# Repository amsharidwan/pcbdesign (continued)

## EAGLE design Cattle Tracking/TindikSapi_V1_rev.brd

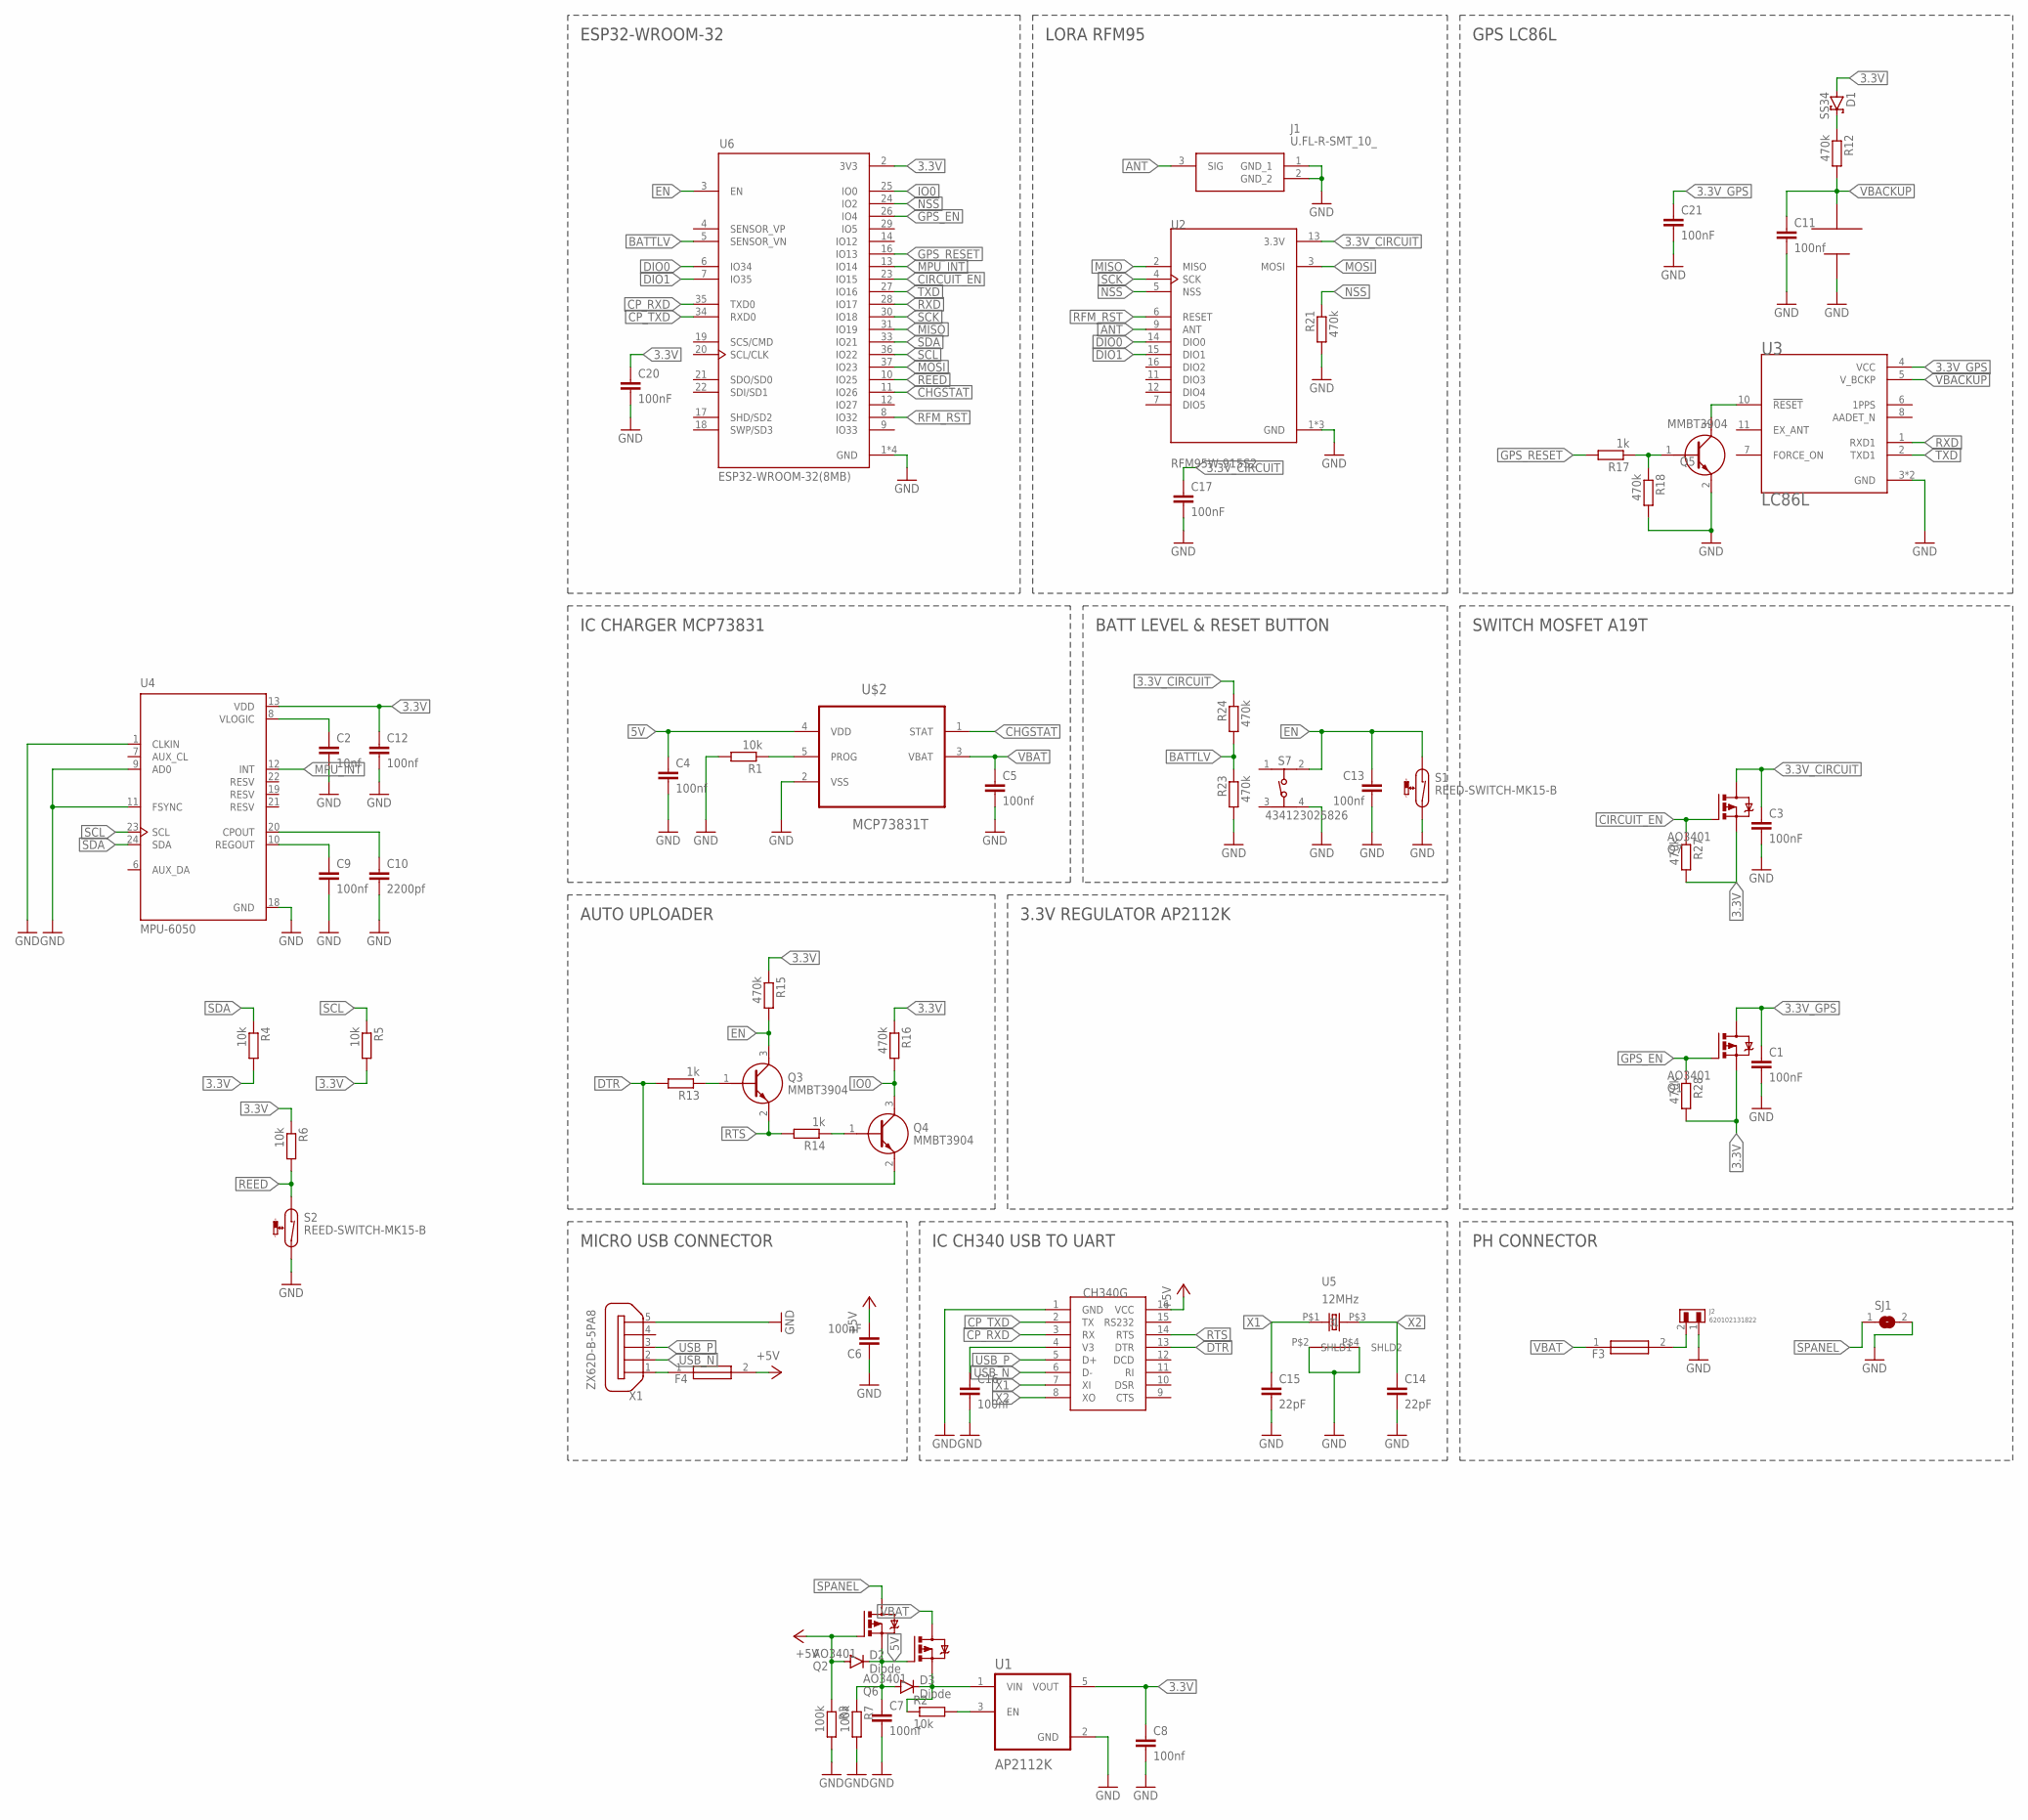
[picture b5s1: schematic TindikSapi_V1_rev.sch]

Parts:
C1, C3, C6, C17, C20, C21: 100nF; C0603
C2: 10nf; C0603
C4, C5, C7, C8, C9, C11, C12, C13, C16: 100nf; C0603
C10: 2200pf; C0603
C14, C15: 22pF; C0603
D1: SS34; SMA
D2, D3: Diode; SOD123
F3, F4: FUSE 1A; FUSC3216X100N
J1: U.FL-R-SMT_10_; UFLRSMT10
J2: 620102131822
Q1, Q2, Q6, Q7: AO3401; SOT23
Q3, Q4, Q5: MMBT3904; SOT95P240X120-3N
R1, R2, R4, R5, R6: 10k; R0603
R3, R7: 100k; R0603
R12, R15, R16, R18, R21, R23, R24, R27, R28: 470k; R0603
R13, R14, R17: 1k; R0603
S1, S2: REED-SWITCH-MK15-B; MK15
S7: 434123025826
SJ1: SJW
U1: AP2112K; SOT95P285X140-5N
U2: RFM95W-915S2; XCVR_RFM95W-915S2
U3: LC86L; XCVR_L86-M33
U4: MPU-6050; QFN50P400X400X95-24N
U5: 12MHz; NX32256A
U6: ESP32-WROOM-32(8MB); MODULE_ESP32-WROOM-32(8MB)
U$2: MCP73831T; SOT95P280X145-5N
U$3: MS621FE
U$5: CH340G; SOIC127P600X175-16N
X1: ZX62D-B-5PA8

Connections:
3.3V: C8.1, C12.1, C20.1, D1.A, Q1.2 (S), Q7.2 (S), R4.2, R5.2, R6.1, R15.1, R16.1, R27.2, R28.2, U1.5 (VOUT), U4.13 (VDD), U6.2 (3V3)
3.3V_CIRCUIT: C3.1, C17.1, Q7.3 (D), R24.1, U2.13 (3.3V)
3.3V_GPS: C1.1, C21.1, Q1.3 (D), U3.4 (VCC)
5V: C4.1, C7.1, D2.C, D3.A, Q2.2 (S), Q6.1 (G), R7.1, U$2.4 (VDD)
+5V: C6.2, D2.A, F4.2, Q2.1 (G), R3.1, U$5.16 (VCC)
ANT: J1.3 (SIG), U2.9 (ANT)
BATTLV: R23.1, R24.2, U6.5 (SENSOR_VN)
CHGSTAT: U6.11 (IO26), U$2.1 (STAT)
CIRCUIT_EN: Q7.1 (G), R27.1, U6.23 (IO15)
CP_RXD: U6.35 (TXD0), U$5.3 (RX)
CP_TXD: U6.34 (RXD0), U$5.2 (TX)
DIO0: U2.14 (DIO0), U6.6 (IO34)
DIO1: U2.15 (DIO1), U6.7 (IO35)
DTR: Q4.2 (E), R13.2, U$5.13 (DTR)
EN: C13.1, Q3.3 (C), R15.2, S1.1, S7.2, U6.3 (EN)
GND: C1.2, C2.2, C3.2, C4.2, C5.2, C6.1, C7.2, C8.2, C9.2, C10.2, C11.2, C12.2, C13.2, C14.2, C15.2, C16.2, C17.2, C20.2, C21.2, J1.1 (GND_1), J1.2 (GND_2), J2.1, Q5.2 (E), R1.2, R3.2, R7.2, R18.2, R21.2, R23.2, S1.2, S2.2, S7.4, SJ1.2, U1.2 (GND), U2.1 (GND), U2.8 (GND), U2.10 (GND), U3.3 (GND), U3.12 (GND), U4.1 (CLKIN), U4.9 (AD0), U4.11 (FSYNC), U4.18 (GND), U5.P$2 (SHLD1), U5.P$4 (SHLD2), U6.1 (GND), U6.15 (GND), U6.38 (GND), U6.39 (GND), U$2.2 (VSS), U$3.V-, U$5.1 (GND), X1.5
GPS_EN: Q1.1 (G), R28.1, U6.26 (IO4)
GPS_RESET: R17.2, U6.16 (IO13)
IO0: Q4.3 (C), R16.2, U6.25 (IO0)
MISO: U2.2 (MISO), U6.31 (IO19)
MOSI: U2.3 (MOSI), U6.37 (IO23)
MPU_INT: U4.12 (INT), U6.13 (IO14)
unnamed: F4.1, X1.1
unnamed: Q5.3 (C), U3.10 (!RESET)
unnamed: Q3.1 (B), R13.1
unnamed: Q4.1 (B), R14.1
unnamed: D3.C, Q6.2 (S), R2.1, U1.1 (VIN)
unnamed: R1.1, U$2.5 (PROG)
unnamed: C2.1, U4.8 (VLOGIC)
unnamed: R2.2, U1.3 (EN)
unnamed: C9.1, U4.10 (REGOUT)
unnamed: C10.1, U4.20 (CPOUT)
unnamed: F3.2, J2.2
unnamed: D1.C, R12.1
unnamed: Q5.1 (B), R17.1, R18.1
unnamed: C16.1, U$5.4 (V3)
NSS: R21.1, U2.5 (NSS), U6.24 (IO2)
REED: R6.2, S2.1, U6.10 (IO25)
RFM_RST: U2.6 (RESET), U6.8 (IO32)
RTS: Q3.2 (E), R14.2, U$5.14 (RTS)
RXD: U3.1 (RXD1), U6.28 (IO17)
SCK: U2.4 (SCK), U6.30 (IO18)
SCL: R5.1, U4.23 (SCL), U6.36 (IO22)
SDA: R4.1, U4.24 (SDA), U6.33 (IO21)
SPANEL: Q2.3 (D), SJ1.1
TXD: U3.2 (TXD1), U6.27 (IO16)
USB_N: U$5.6 (D-), X1.2
USB_P: U$5.5 (D+), X1.3
VBACKUP: C11.1, R12.2, U3.5 (V_BCKP), U$3.V+
VBAT: C5.1, F3.1, Q6.3 (D), U$2.3 (VBAT)
X1: C15.1, U5.P$1 (1), U$5.7 (XI)
X2: C14.1, U5.P$3 (3), U$5.8 (XO)

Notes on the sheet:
MICRO USB CONNECTOR
IC CH340 USB TO UART
AUTO UPLOADER
PH CONNECTOR
3.3V REGULATOR AP2112K
SWITCH MOSFET A19T
BATT LEVEL & RESET BUTTON
IC CHARGER MCP73831
ESP32-WROOM-32
LORA RFM95
GPS LC86L

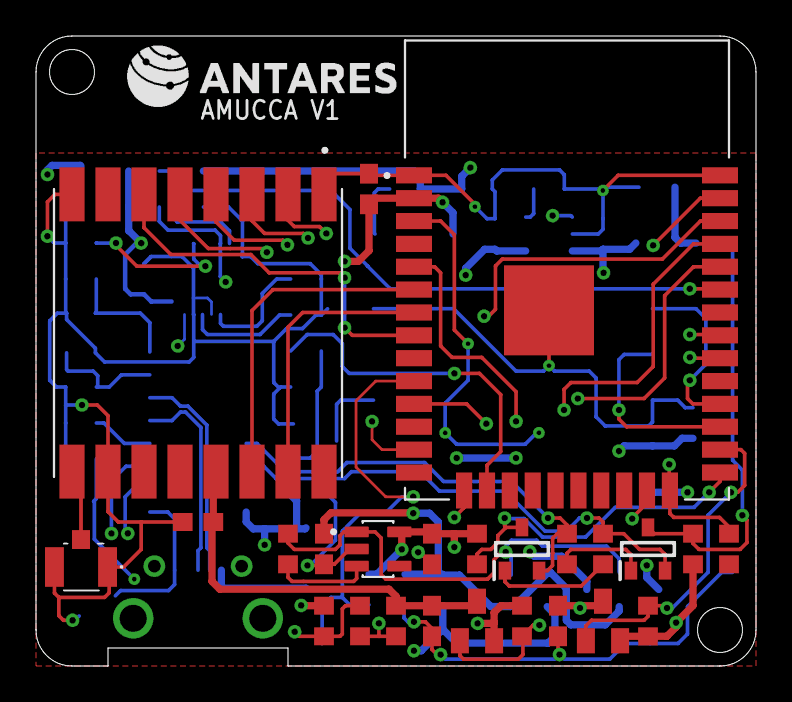
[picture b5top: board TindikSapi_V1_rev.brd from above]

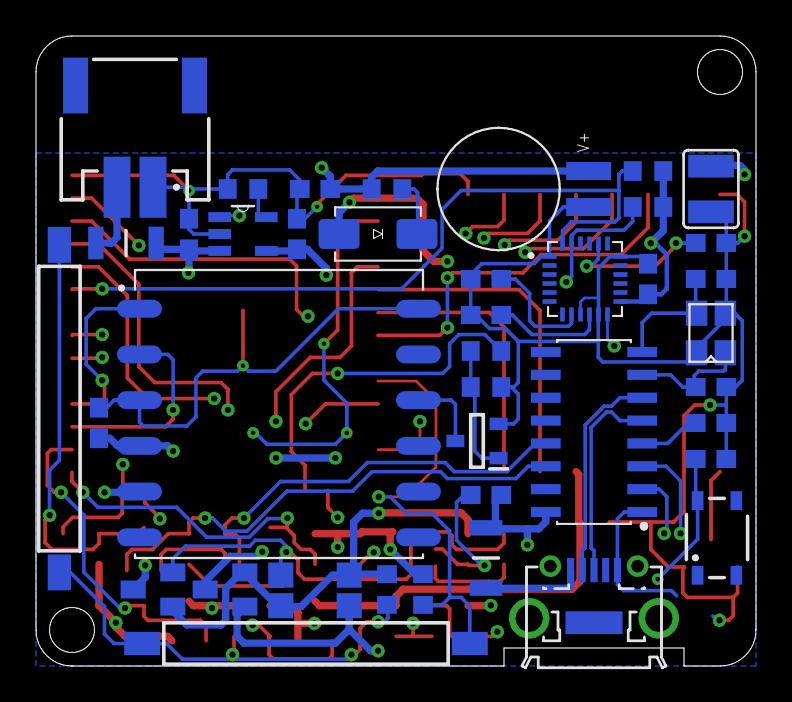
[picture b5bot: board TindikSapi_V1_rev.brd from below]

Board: 4 copper layers, 40.0 x 35.0 mm, 66 parts (41 on the bottom side), 52 nets.

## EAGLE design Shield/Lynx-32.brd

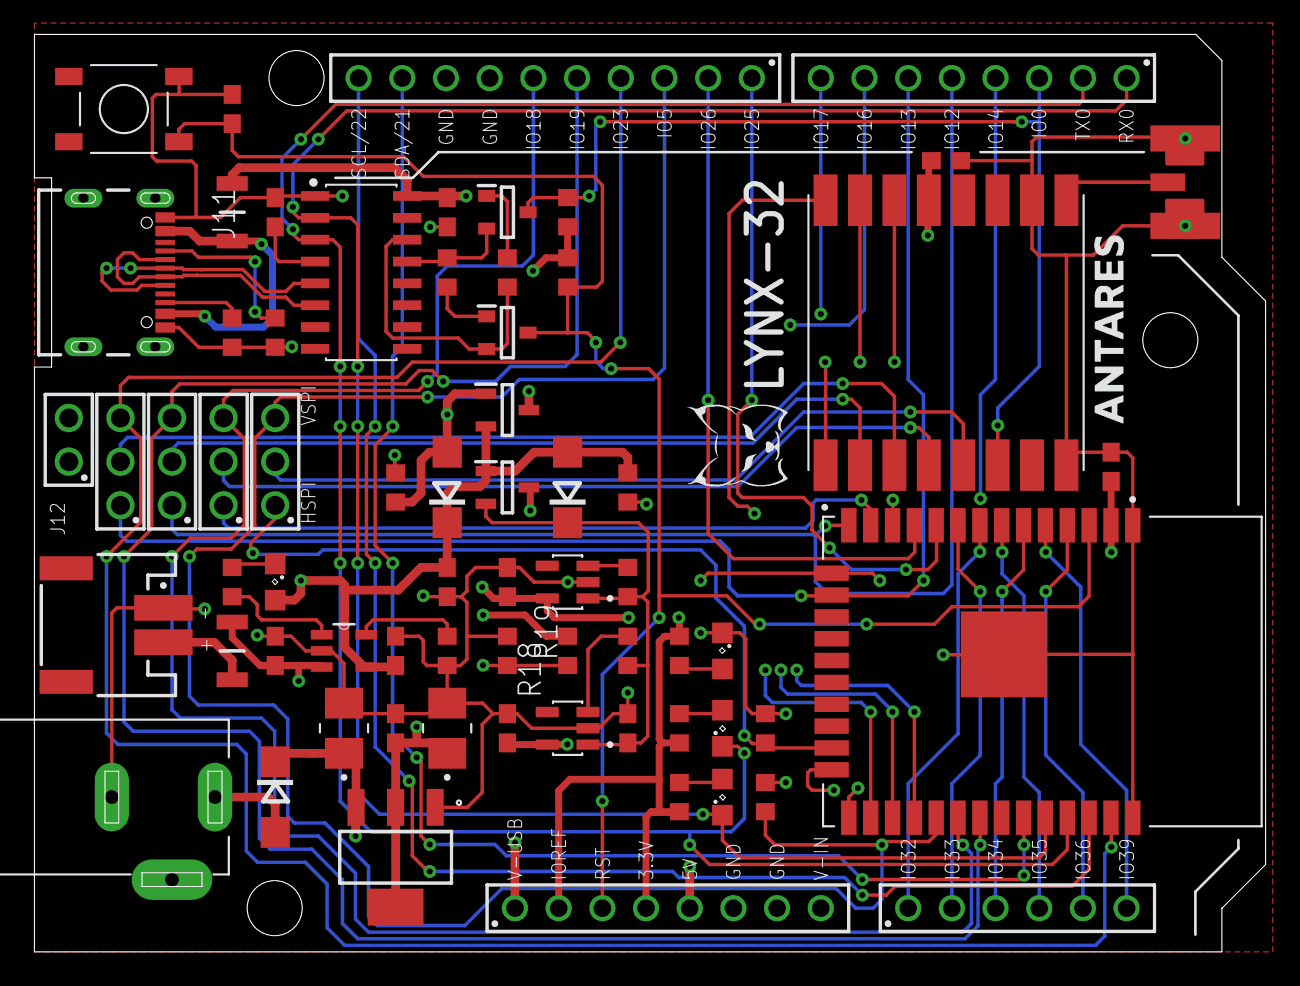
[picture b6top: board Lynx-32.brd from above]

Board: 4 copper layers, 71.6 x 53.3 mm, 67 parts (0 on the bottom side), 63 nets.

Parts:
C1, C2, C3, C4, C5, C6, C9, C10, C11, C12, C14, C15: 100nF; C0603
C7, C8: T543B106M025ATS100; CAPPM3528X210N
D1, D2, D3: DO214AC
F1, F2: MF-NSML260_12-2; FUSC3216X100N
J1: 61300611821
J2, J3: 61300811821
J4: 61301011821
J5: DC-005; NINIGI_DC-005
J6, J7, J8, J9: 61300311121
J10: 620102131822
J11: USB4105-GF-A; GCT_USB4105-GF-A
J12: 61300211121
LED1, LED2, LED3, LED4: SML0805
Q1, Q2: AO3401A; SOT95P280X125-3N
Q3, Q4: MMBT3904; SOT95P240X120-3N
R1, R2, R18, R19: 5.1K; R0603
R3, R4, R14: 2K; R0603
R5, R7: 1K; R0603
R6, R8, R11, R12, R13, R15, R17: 10K; R0603
R9, R10: 100K; R0603
R16: 470R; R0603
S1: PTS525SM15SMTR2LFS; SW_PTS525SM15SMTR2LFS
U1: ESP32-WROOM-32(8MB); MODULE_ESP32-WROOM-32(8MB)
U2: RFM95W-915S2; XCVR_RFM95W-915S2
U3, U4: AP2112K-3.3TRG1; SOT95P285X140-5N
U5: LD1117S50TR; SOT230P700X180-4N
U$1: SMA
U$2: CH340G-3D; SOIC127P600X175-16N
U$3: MCP73831T-5ACI/OT; SOT95P280X145-5N

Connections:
3.3V: C4.1, C14.1, J2.2, J2.4, R3.2, R4.2, R6.2, R8.1, R14.2, U1.2, U3.5
3.3V_RFM: C6.1, C15.1, U2.13, U4.5
5V: C3.1, C11.1, D1.C, D2.A, J2.5, LED4.A, Q1.2, Q2.1, R10.2, U$3.4
5V_REG: C8.1, C9.1, D1.A, Q1.1, R9.2, U5.2, U5.4
5V_USB: C1.1, F1.1, J2.1, Q1.3, U$2.16
ANT: U2.9, U$1.P
BATLV: J12.1, R18.2, R19.1
CP_RXD: J3.2, LED1.C, U1.35, U$2.3
CP_TXD: J3.1, LED2.C, U1.34, U$2.2
DTR: Q4.2, R5.1, U$2.13
EN: C12.1, J2.3, Q3.3, R6.1, S1.4, U1.3
GND: C1.2, C2.2, C3.2, C4.2, C5.2, C6.2, C7.2, C8.2, C9.2, C10.2, C11.2, C12.2, C14.2, C15.2, J2.6, J2.7, J4.7, J4.8, J5.3, J10.1, J11.A1_B12, J11.B1_A12, LED3.C, R1.1, R2.1, R9.1, R10.1, R13.1, R15.1, R17.1, R18.1, S1.2, U1.1, U1.15, U1.38, U1.39, U2.1, U2.8, U2.10, U3.2, U4.2, U5.1, U$1.GND@1, U$1.GND@2, U$1.GND@3, U$1.GND@4, U$2.1, U$3.2
IO0: J3.3, Q4.3, R8.2, U1.25, U2.6
IO2: U1.24, U2.15
IO4: U1.26, U2.16
IO5: J4.3, J9.3, R17.2, U1.29
IO12: J3.5, J7.1, U1.14
IO13: J3.6, J6.1, U1.16
IO14: J3.4, J8.1, U1.13
IO15: J9.1, R15.2, U1.23
IO16: J3.7, U1.27
IO17: J3.8, U1.28
IO18: J4.6, J8.3, U1.30
IO19: J4.5, J7.3, U1.31
IO21: J4.9, U1.33
IO22: J4.10, U1.36
IO23: J4.4, J6.3, U1.37
IO25: J4.1, U1.10
IO26: J4.2, U1.11
IO27: U1.12, U2.14
IO32: J1.1, U1.8
IO33: J1.2, U1.9
IO34: J1.3, U1.6
IO35: J1.4, U1.7
IO36: J1.5, U1.4
IO39: J1.6, J12.2, U1.5
MISO: J7.2, U2.2
MOSI: J6.2, U2.3
unnamed: F1.2, J11.A4_B9, J11.B4_A9
unnamed: J11.B5, R2.2
unnamed: LED3.A, R14.1
unnamed: F2.2, J10.2
unnamed: J11.A5, R1.2
unnamed: C5.1, D2.C, Q2.2, R11.1, R12.1, U3.1, U4.1
unnamed: C2.1, U$2.4
unnamed: LED1.A, R3.1
unnamed: LED2.A, R4.1
unnamed: R11.2, U3.3
unnamed: R12.2, U4.3
unnamed: D3.A, J5.4
unnamed: R13.2, U$3.5
unnamed: Q4.1, R7.1
unnamed: Q3.1, R5.2
unnamed: LED4.C, R16.2
unnamed: R16.1, U$3.1
NSS: J9.2, U2.5
RTS: Q3.2, R7.2, U$2.14
SCK: J8.2, U2.4
SHELL_GND: J11.S1, J11.S2, J11.S3, J11.S4
USB_N: J11.A7, J11.B7, U$2.6
USB_P: J11.A6, J11.B6, U$2.5
V-IN: C7.1, D3.C, J2.8, U5.3
VBAT: C10.1, F2.1, Q2.3, R19.2, U$3.3

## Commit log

2021-10-23 PCB Design
